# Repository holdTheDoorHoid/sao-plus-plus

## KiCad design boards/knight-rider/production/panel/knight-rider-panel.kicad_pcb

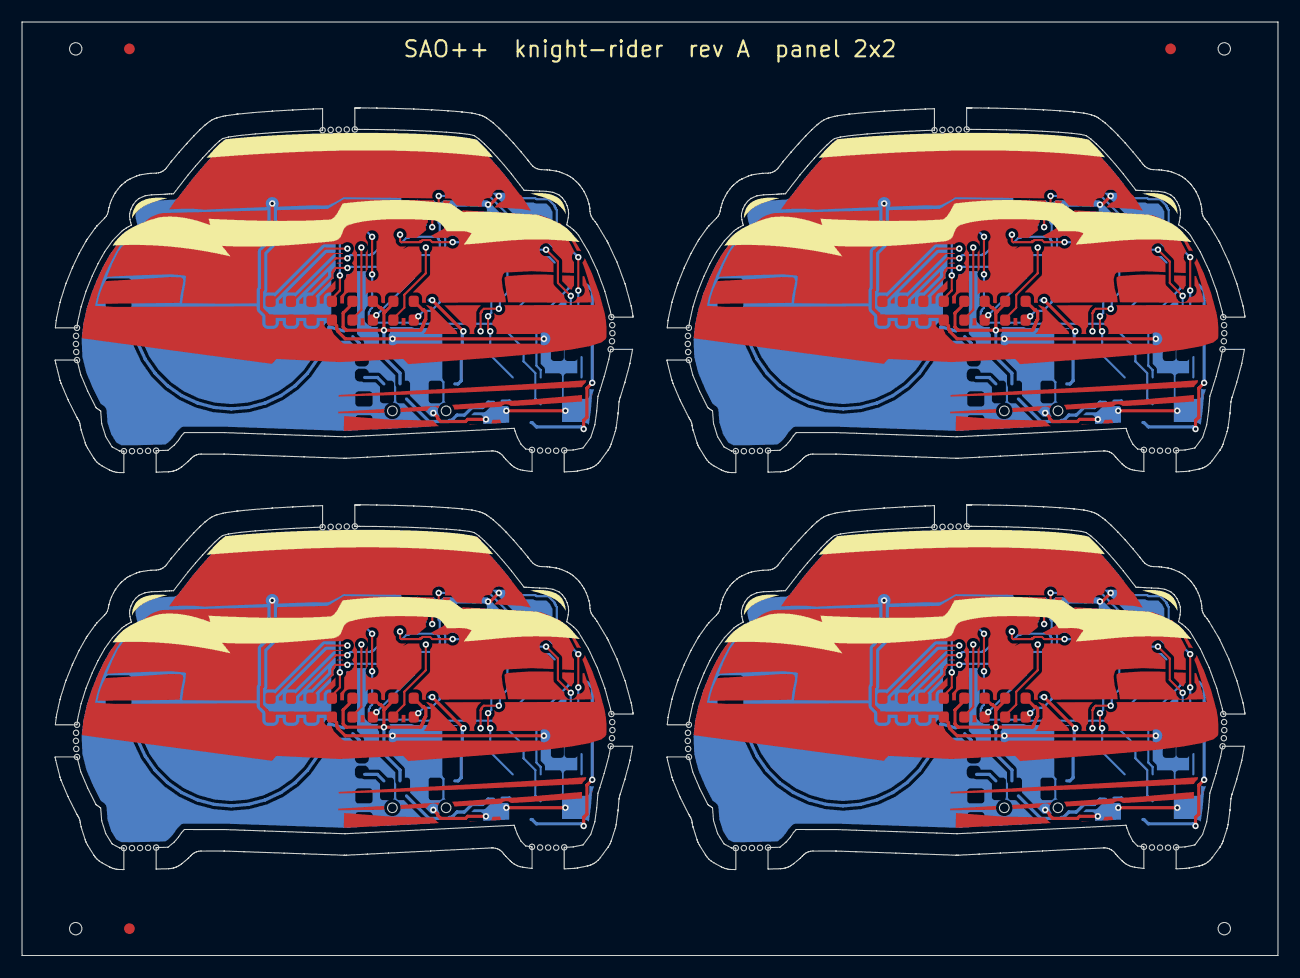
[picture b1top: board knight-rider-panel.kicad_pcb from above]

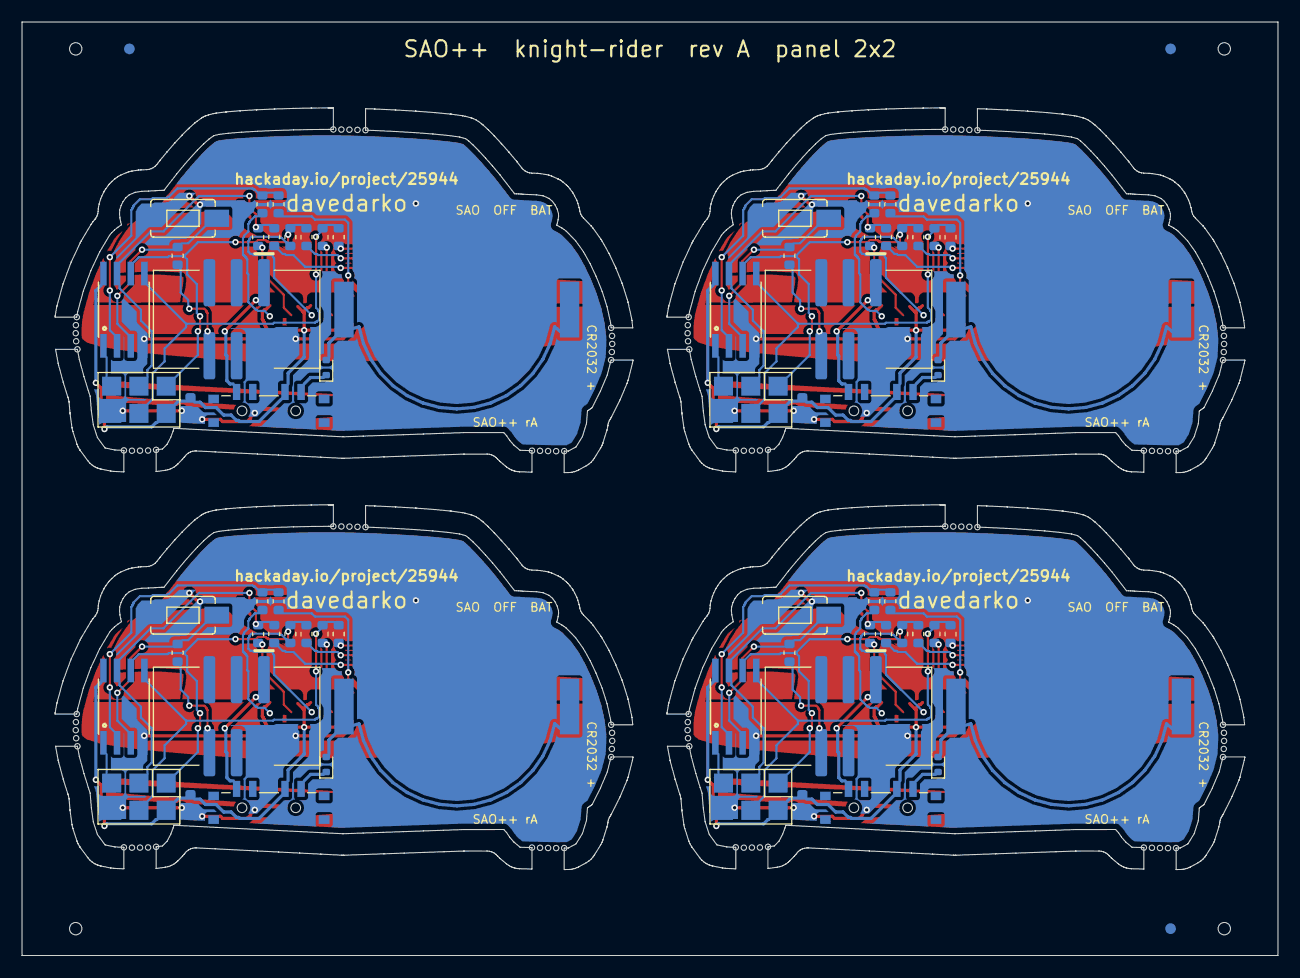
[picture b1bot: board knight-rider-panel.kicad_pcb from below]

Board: 2 copper layers, 117.0 x 86.9 mm, 100 parts (68 on the bottom side), 80 nets.

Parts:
BT101, BT201, BT301, BT401: CR2032; SAOPP_BAT-01_CR2032_SMD_TE_BAT-HLD-001
C101, C201, C301, C401: 100n; SAOPP_C_0603_1608Metric
D101, D102, D103, D104, D105, D106, D107, D108, D201, D202, D203, D204, D205, D206, D207, D208, D301, D302, D303, D304, D305, D306, D307, D308, D401, D402, D403, D404, D405, D406, D407, D408: red; LED_0603_1608Metric_Pad1.05x0.95mm_HandSolder
D109, D209, D309, D409: RB751S40; D_SOD-523
J101, J201, J301, J401: SAO v1.69bis; SAOPP_CONN-01_BoxHeader_2x03_P2.54mm_SMD_XFCN_BH254VS-6P
JP101, JP201, JP301, JP401: ISP pads; 2X3_SMD_PAD
R101, R102, R103, R104, R105, R106, R107, R108, R201, R202, R203, R204, R205, R206, R207, R208, R301, R302, R303, R304, R305, R306, R307, R308, R401, R402, R403, R404, R405, R406, R407, R408: 1.3k; SAOPP_R_0603_1608Metric
R109, R209, R309, R409: 330; SAOPP_R_0603_1608Metric
SW101, SW201, SW301, SW401: SAO / OFF / BAT; SAOPP_SW-01_Slide_SP3T_CK_PCM13SMTR
SW102, SW202, SW302, SW402: button; TACTILE-SWITCH-1101NE
U101, U201, U301, U401: ATtiny85V; SO08-EIAJ

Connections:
B2-GND: BT201.2, C201.2, D201.1, D202.1, D203.1, D204.1, J201.2, JP201.P$6, SW202.P$2, U201.4
B2-LED1_A: D201.2, R205.2
B2-LED2_A: D202.2, R206.2
B2-LED3_A: D203.2, R207.2
B2-LED4_A: D204.2, R208.2
B2-LED5_K: D205.1, R201.2
B2-LED6_K: D206.1, R202.2
B2-LED7_K: D207.1, R203.2
B2-LED8_K: D208.1, R204.2
B2-MISO: JP201.P$1, R202.1, R206.1, U201.6
B2-MOSI: JP201.P$4, R201.1, R205.1, U201.5
B2-PB3: R204.1, R208.1, U201.2
B2-PB4: R209.1, SW202.P$1, U201.3
B2-RST: JP201.P$5, U201.1
B2-SAO_GPIO2: J201.6, R209.2
B2-SCK: JP201.P$3, R203.1, R207.1, U201.7
B2-VBAT: D209.1, SW201.4
B2-VCELL: BT201.1, D209.2
B2-VLOAD: C201.1, D205.2, D206.2, D207.2, D208.2, JP201.P$2, SW201.3, U201.8
B2-VSAO: J201.1, SW201.1
B3-GND: BT301.2, C301.2, D301.1, D302.1, D303.1, D304.1, J301.2, JP301.P$6, SW302.P$2, U301.4
B3-LED1_A: D301.2, R305.2
B3-LED2_A: D302.2, R306.2
B3-LED3_A: D303.2, R307.2
B3-LED4_A: D304.2, R308.2
B3-LED5_K: D305.1, R301.2
B3-LED6_K: D306.1, R302.2
B3-LED7_K: D307.1, R303.2
B3-LED8_K: D308.1, R304.2
B3-MISO: JP301.P$1, R302.1, R306.1, U301.6
B3-MOSI: JP301.P$4, R301.1, R305.1, U301.5
B3-PB3: R304.1, R308.1, U301.2
B3-PB4: R309.1, SW302.P$1, U301.3
B3-RST: JP301.P$5, U301.1
B3-SAO_GPIO2: J301.6, R309.2
B3-SCK: JP301.P$3, R303.1, R307.1, U301.7
B3-VBAT: D309.1, SW301.4
B3-VCELL: BT301.1, D309.2
B3-VLOAD: C301.1, D305.2, D306.2, D307.2, D308.2, JP301.P$2, SW301.3, U301.8
B3-VSAO: J301.1, SW301.1
B4-GND: BT401.2, C401.2, D401.1, D402.1, D403.1, D404.1, J401.2, JP401.P$6, SW402.P$2, U401.4
B4-LED1_A: D401.2, R405.2
B4-LED2_A: D402.2, R406.2
B4-LED3_A: D403.2, R407.2
B4-LED4_A: D404.2, R408.2
B4-LED5_K: D405.1, R401.2
B4-LED6_K: D406.1, R402.2
B4-LED7_K: D407.1, R403.2
B4-LED8_K: D408.1, R404.2
B4-MISO: JP401.P$1, R402.1, R406.1, U401.6
B4-MOSI: JP401.P$4, R401.1, R405.1, U401.5
B4-PB3: R404.1, R408.1, U401.2
B4-PB4: R409.1, SW402.P$1, U401.3
B4-RST: JP401.P$5, U401.1
B4-SAO_GPIO2: J401.6, R409.2
B4-SCK: JP401.P$3, R403.1, R407.1, U401.7
B4-VBAT: D409.1, SW401.4
B4-VCELL: BT401.1, D409.2
B4-VLOAD: C401.1, D405.2, D406.2, D407.2, D408.2, JP401.P$2, SW401.3, U401.8
B4-VSAO: J401.1, SW401.1
GND: BT101.2, C101.2, D101.1, D102.1, D103.1, D104.1, J101.2, JP101.P$6, SW102.P$2, U101.4
LED1_A: D101.2, R105.2
LED2_A: D102.2, R106.2
LED3_A: D103.2, R107.2
LED4_A: D104.2, R108.2
LED5_K: D105.1, R101.2
LED6_K: D106.1, R102.2
LED7_K: D107.1, R103.2
LED8_K: D108.1, R104.2
MISO: JP101.P$1, R102.1, R106.1, U101.6
MOSI: JP101.P$4, R101.1, R105.1, U101.5
PB3: R104.1, R108.1, U101.2
PB4: R109.1, SW102.P$1, U101.3
RST: JP101.P$5, U101.1
SAO_GPIO2: J101.6, R109.2
SCK: JP101.P$3, R103.1, R107.1, U101.7
VBAT: D109.1, SW101.4
VCELL: BT101.1, D109.2
VLOAD: C101.1, D105.2, D106.2, D107.2, D108.2, JP101.P$2, SW101.3, U101.8
VSAO: J101.1, SW101.1

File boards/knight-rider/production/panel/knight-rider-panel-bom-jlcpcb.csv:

Comment,Designator,Footprint,LCSC Part #
CR2032,"BT101,BT201,BT301,BT401",SAOPP_BAT-01_CR2032_SMD_TE_BAT-HLD-001,C7501066
100n,"C101,C201,C301,C401",SAOPP_C_0603_1608Metric,C14663
red,"D101,D102,D103,D104,D105,D106,D107,D108,D201,D202,D203,D204,D205,D206,D207,D208,D301,D302,D303,D304,D305,D306,D307,D308,D401,D402,D403,D404,D405,D406,D407,D408",LED_0603_1608Metric_Pad1.05x0.95mm_HandSolder,C125099
RB751S40,"D109,D209,D309,D409",D_SOD-523,C232576
SAO v1.69bis,"J101,J201,J301,J401",SAOPP_CONN-01_BoxHeader_2x03_P2.54mm_SMD_XFCN_BH254VS-6P,C492445
ISP pads,"JP101,JP201,JP301,JP401",2X3_SMD_PAD,
1.3k,"R101,R102,R103,R104,R105,R106,R107,R108,R201,R202,R203,R204,R205,R206,R207,R208,R301,R302,R303,R304,R305,R306,R307,R308,R401,R402,R403,R404,R405,R406,R407,R408",SAOPP_R_0603_1608Metric,C22767
330,"R109,R209,R309,R409",SAOPP_R_0603_1608Metric,C23138
SAO / OFF / BAT,"SW101,SW201,SW301,SW401",SAOPP_SW-01_Slide_SP3T_CK_PCM13SMTR,C221842
button,"SW102,SW202,SW302,SW402",TACTILE-SWITCH-1101NE,
ATtiny85V,"U101,U201,U301,U401",SO08-EIAJ,C152192

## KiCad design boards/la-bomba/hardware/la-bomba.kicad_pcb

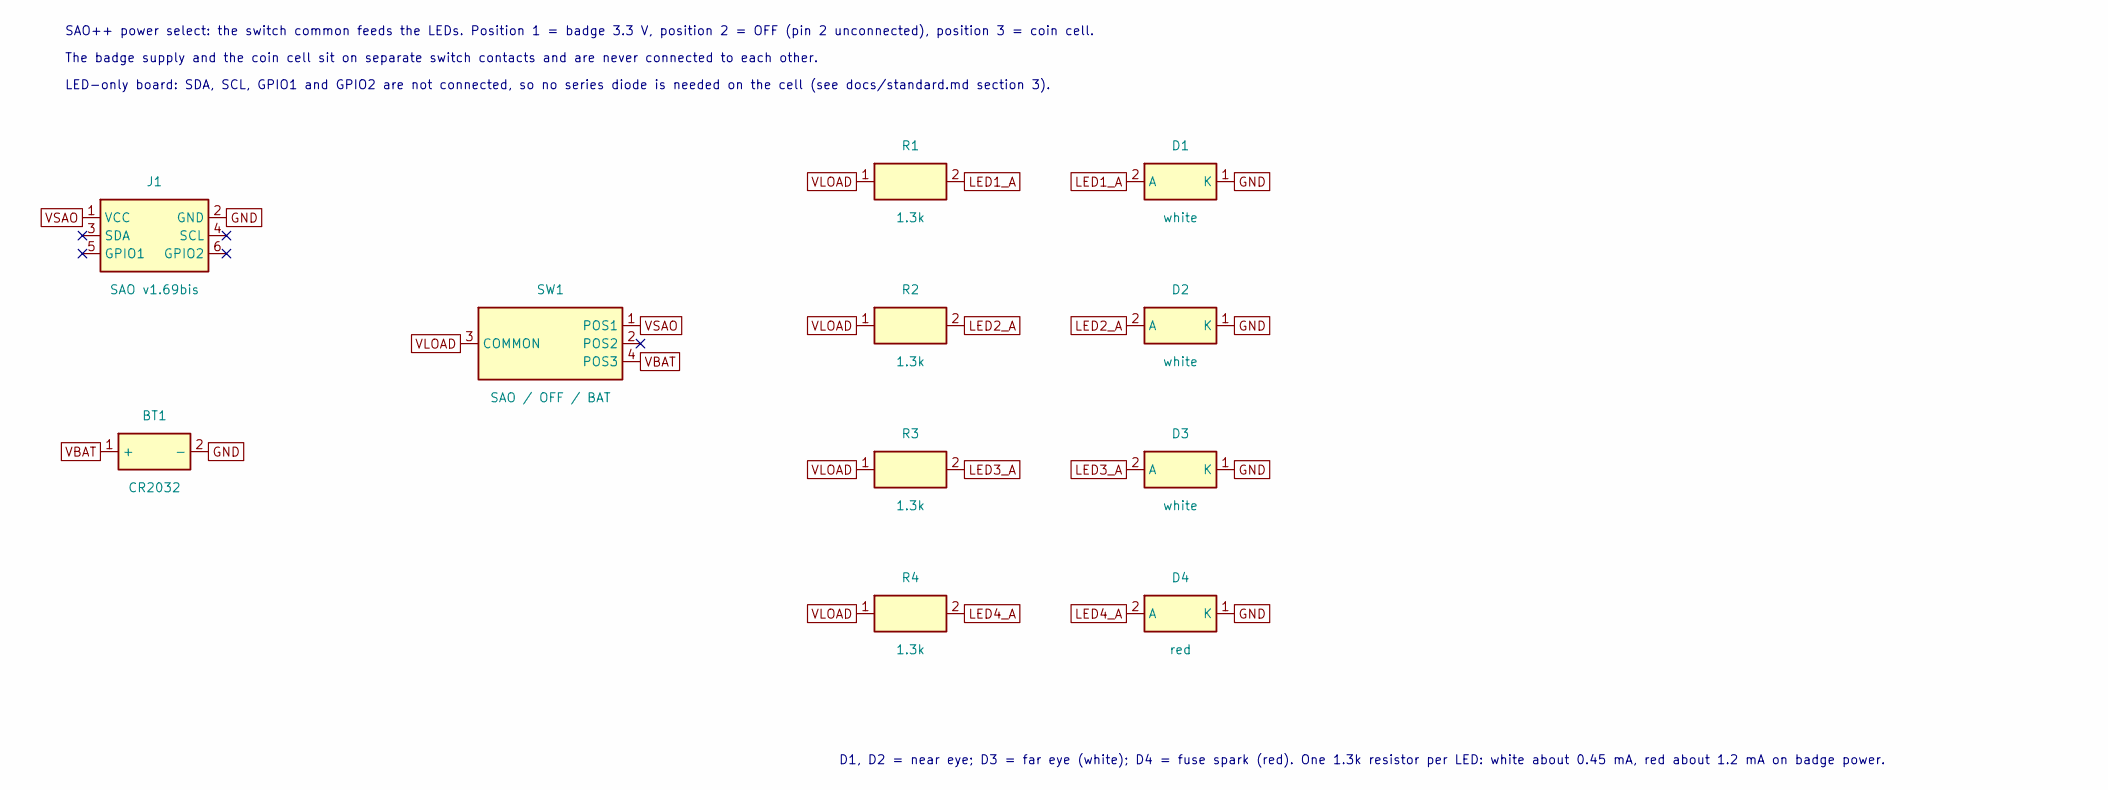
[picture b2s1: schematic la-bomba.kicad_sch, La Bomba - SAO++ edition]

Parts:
BT1: CR2032; SAOPP_BAT-01_CR2032_SMD_TE_BAT-HLD-001; MPN BAT-HLD-001; LCSC C7501066
D1, D2, D3: white; SAOPP_LED-10_1206_ReverseMount_ThroughBoard; MPN LTW-C230DS; LCSC C575513
D4: red; SAOPP_LED-10_1206_ReverseMount_ThroughBoard; MPN LTST-C230KRKT; LCSC C125107
J1: SAO v1.69bis; SAOPP_CONN-01_BoxHeader_2x03_P2.54mm_SMD_XFCN_BH254VS-6P; MPN BH254VS-6P; LCSC C492445
R1, R2, R3, R4: 1.3k; SAOPP_R_0603_1608Metric; MPN 0603WAF1301T5E; LCSC C22767
SW1: SAO / OFF / BAT; SAOPP_SW-01_Slide_SP3T_CK_PCM13SMTR; MPN PCM13SMTR; LCSC C221842

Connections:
GND: BT1.2 (-), D1.1 (K), D2.1 (K), D3.1 (K), D4.1 (K), J1.2 (GND)
LED1_A: D1.2 (A), R1.2
LED2_A: D2.2 (A), R2.2
LED3_A: D3.2 (A), R3.2
LED4_A: D4.2 (A), R4.2
VBAT: BT1.1 (+), SW1.4 (POS3)
VLOAD: R1.1, R2.1, R3.1, R4.1, SW1.3 (COMMON)
VSAO: J1.1 (VCC), SW1.1 (POS1)

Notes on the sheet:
SAO++ power select: the switch common feeds the LEDs. Position 1 = badge 3.3 V, position 2 = OFF (pin 2 unconnected), position 3 = coin cell.
The badge supply and the coin cell sit on separate switch contacts and are never connected to each other.
LED-only board: SDA, SCL, GPIO1 and GPIO2 are not connected, so no series diode is needed on the cell (see docs/standard.md section 3).
D1, D2 = near eye; D3 = far eye (white); D4 = fuse spark (red). One 1.3k resistor per LED: white about 0.45 mA, red about 1.2 mA on badge power.

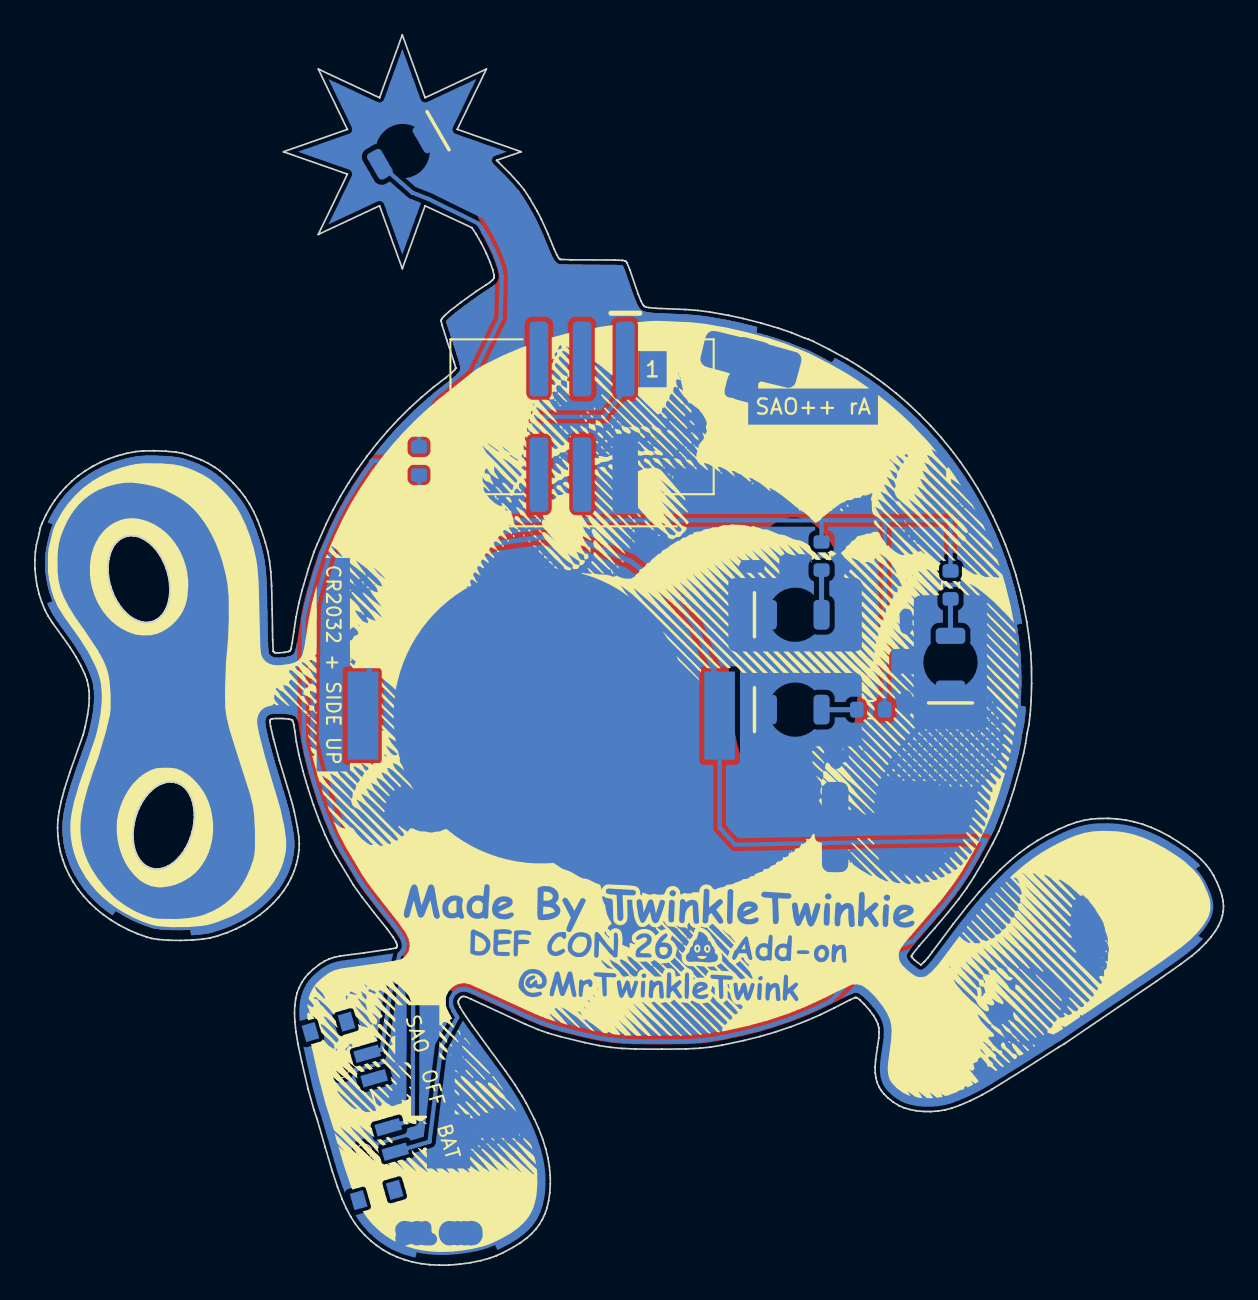
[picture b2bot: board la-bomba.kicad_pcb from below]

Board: 2 copper layers, 70.0 x 72.5 mm, 15 parts (11 on the bottom side), 8 nets.

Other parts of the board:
B.Silk: LOGO; B.Silk_g1544
F.Cu, F.Silk: LOGO
F.Mask: LOGO; F.Mask_g1548

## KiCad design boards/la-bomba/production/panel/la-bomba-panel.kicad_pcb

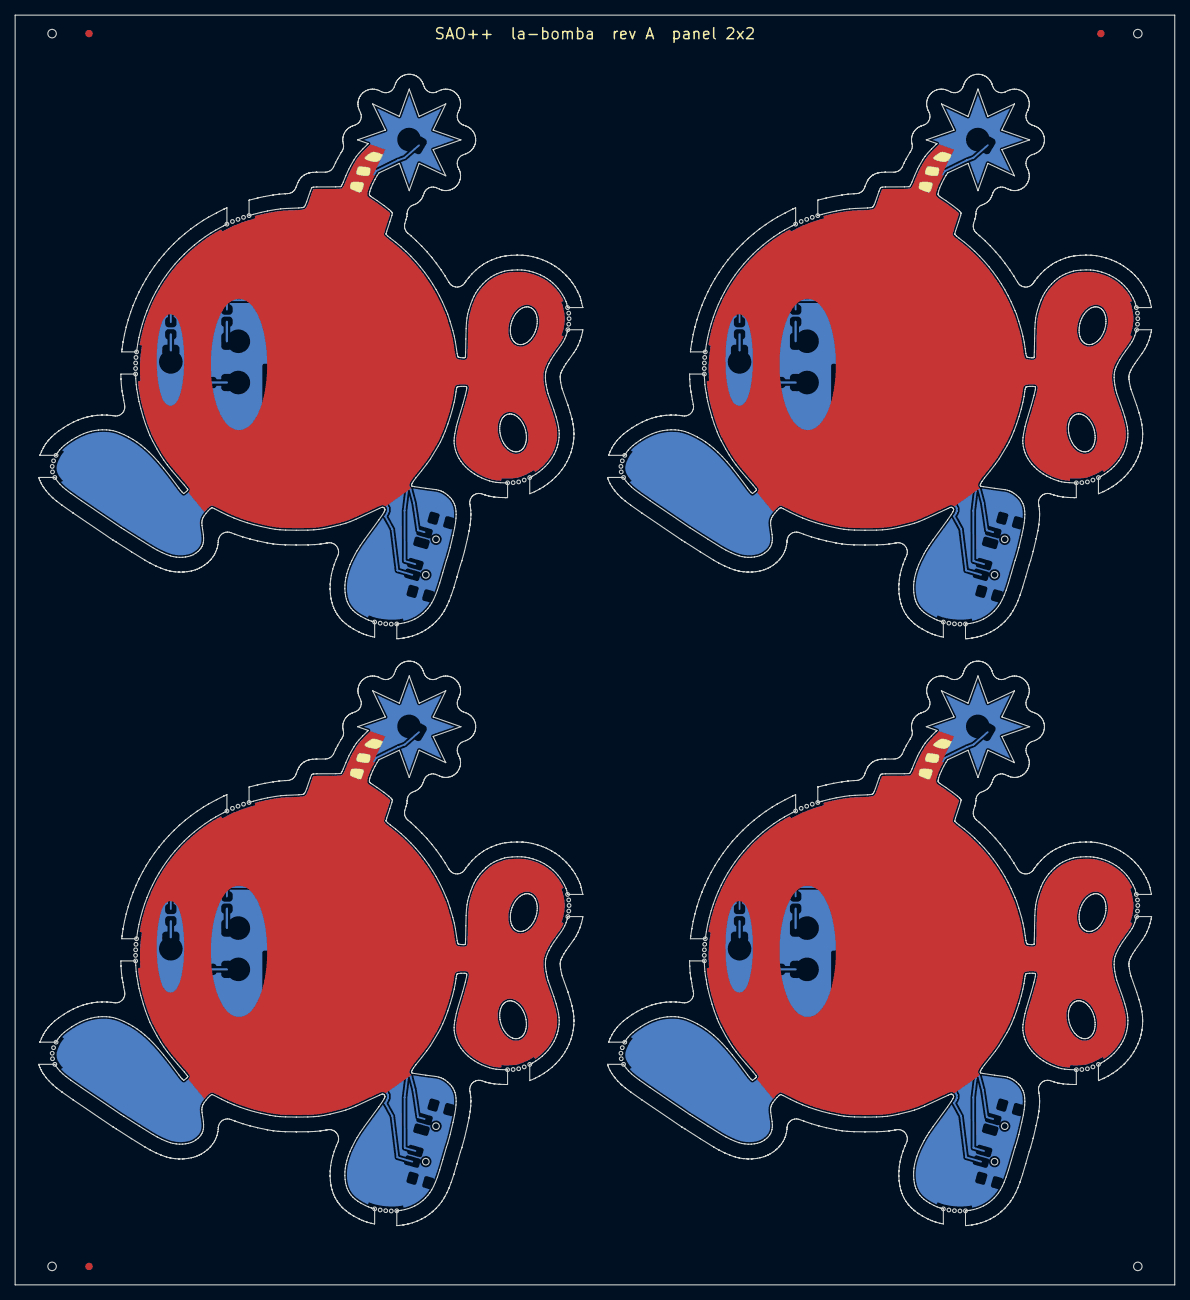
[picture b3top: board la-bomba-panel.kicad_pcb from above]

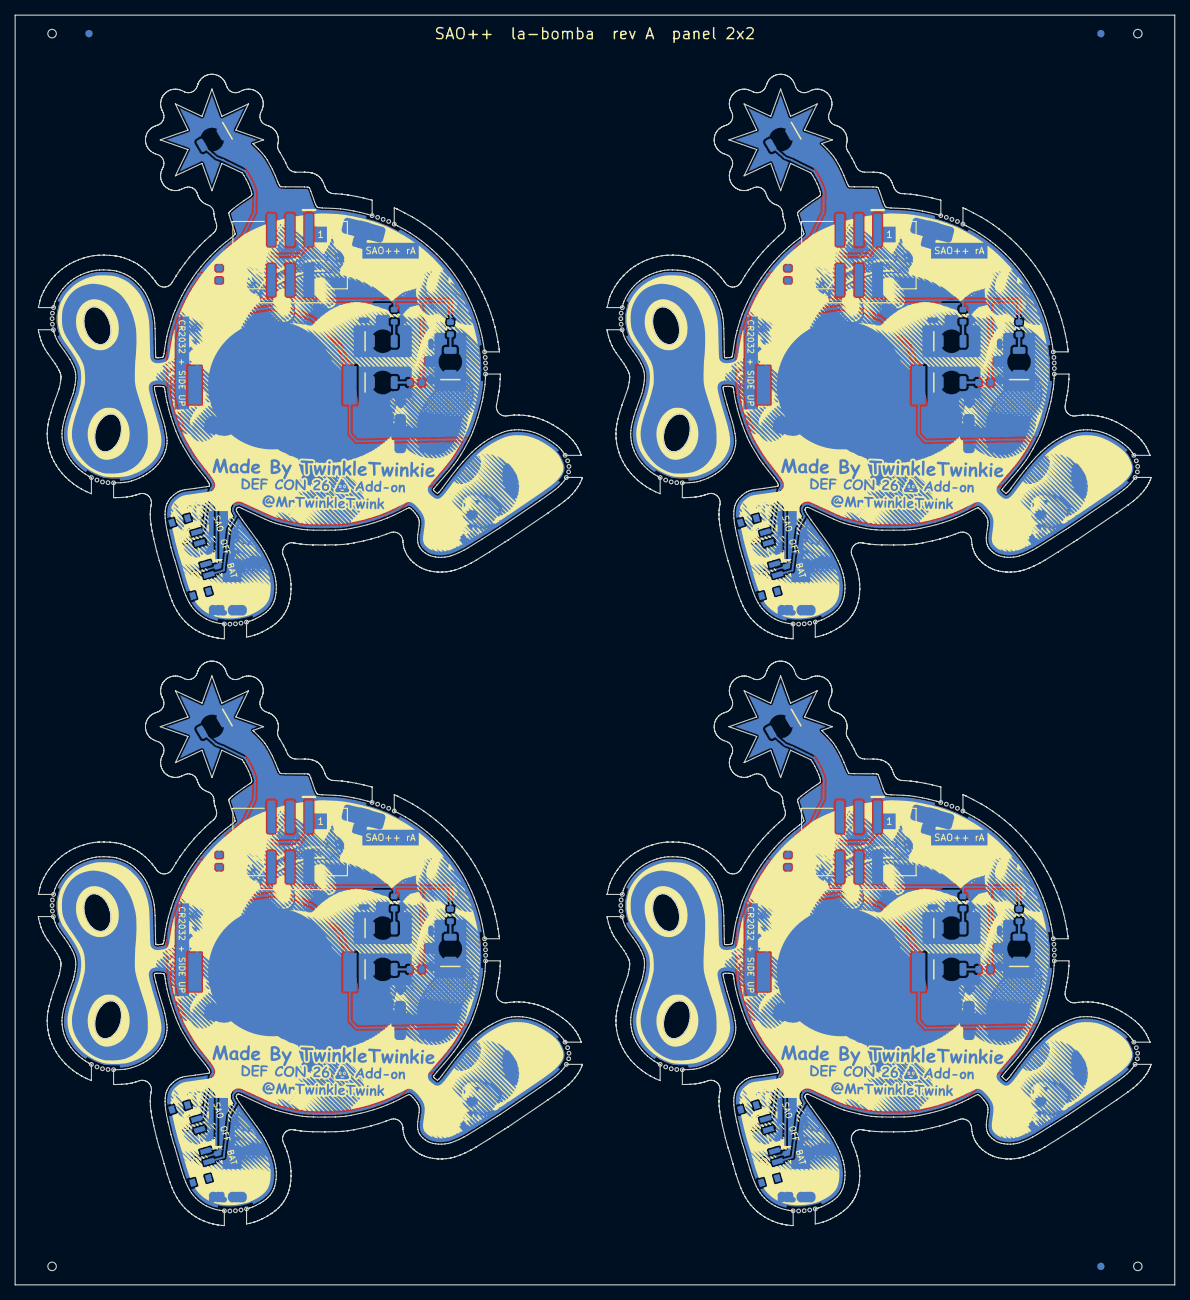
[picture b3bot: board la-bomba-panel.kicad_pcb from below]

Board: 2 copper layers, 157.0 x 171.9 mm, 60 parts (44 on the bottom side), 32 nets.

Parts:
B.Silk, B.Silk#2, B.Silk#3, B.Silk#4: LOGO; B.Silk_g1544
BT101, BT201, BT301, BT401: CR2032; SAOPP_BAT-01_CR2032_SMD_TE_BAT-HLD-001
D101, D102, D103, D201, D202, D203, D301, D302, D303, D401, D402, D403: white; SAOPP_LED-10_1206_ReverseMount_ThroughBoard
D104, D204, D304, D404: red; SAOPP_LED-10_1206_ReverseMount_ThroughBoard
F.Cu, F.Cu#2, F.Cu#3, F.Cu#4, F.Silk, F.Silk#2, F.Silk#3, F.Silk#4: LOGO
F.Mask, F.Mask#2, F.Mask#3, F.Mask#4: LOGO; F.Mask_g1548
J101, J201, J301, J401: SAO v1.69bis; SAOPP_CONN-01_BoxHeader_2x03_P2.54mm_SMD_XFCN_BH254VS-6P
R101, R102, R103, R104, R201, R202, R203, R204, R301, R302, R303, R304, R401, R402, R403, R404: 1.3k; SAOPP_R_0603_1608Metric
SW101, SW201, SW301, SW401: SAO / OFF / BAT; SAOPP_SW-01_Slide_SP3T_CK_PCM13SMTR

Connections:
B2-GND: BT201.2, D201.1, D202.1, D203.1, D204.1, J201.2
B2-LED1_A: D201.2, R201.2
B2-LED2_A: D202.2, R202.2
B2-LED3_A: D203.2, R203.2
B2-LED4_A: D204.2, R204.2
B2-VBAT: BT201.1, SW201.4
B2-VLOAD: R201.1, R202.1, R203.1, R204.1, SW201.3
B2-VSAO: J201.1, SW201.1
B3-GND: BT301.2, D301.1, D302.1, D303.1, D304.1, J301.2
B3-LED1_A: D301.2, R301.2
B3-LED2_A: D302.2, R302.2
B3-LED3_A: D303.2, R303.2
B3-LED4_A: D304.2, R304.2
B3-VBAT: BT301.1, SW301.4
B3-VLOAD: R301.1, R302.1, R303.1, R304.1, SW301.3
B3-VSAO: J301.1, SW301.1
B4-GND: BT401.2, D401.1, D402.1, D403.1, D404.1, J401.2
B4-LED1_A: D401.2, R401.2
B4-LED2_A: D402.2, R402.2
B4-LED3_A: D403.2, R403.2
B4-LED4_A: D404.2, R404.2
B4-VBAT: BT401.1, SW401.4
B4-VLOAD: R401.1, R402.1, R403.1, R404.1, SW401.3
B4-VSAO: J401.1, SW401.1
GND: BT101.2, D101.1, D102.1, D103.1, D104.1, J101.2
LED1_A: D101.2, R101.2
LED2_A: D102.2, R102.2
LED3_A: D103.2, R103.2
LED4_A: D104.2, R104.2
VBAT: BT101.1, SW101.4
VLOAD: R101.1, R102.1, R103.1, R104.1, SW101.3
VSAO: J101.1, SW101.1

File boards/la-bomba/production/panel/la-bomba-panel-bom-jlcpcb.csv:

Comment,Designator,Footprint,LCSC Part #
CR2032,"BT101,BT201,BT301,BT401",SAOPP_BAT-01_CR2032_SMD_TE_BAT-HLD-001,C7501066
white,"D101,D102,D103,D201,D202,D203,D301,D302,D303,D401,D402,D403",SAOPP_LED-10_1206_ReverseMount_ThroughBoard,C575513
red,"D104,D204,D304,D404",SAOPP_LED-10_1206_ReverseMount_ThroughBoard,C125107
SAO v1.69bis,"J101,J201,J301,J401",SAOPP_CONN-01_BoxHeader_2x03_P2.54mm_SMD_XFCN_BH254VS-6P,C492445
1.3k,"R101,R102,R103,R104,R201,R202,R203,R204,R301,R302,R303,R304,R401,R402,R403,R404",SAOPP_R_0603_1608Metric,C22767
SAO / OFF / BAT,"SW101,SW201,SW301,SW401",SAOPP_SW-01_Slide_SP3T_CK_PCM13SMTR,C221842

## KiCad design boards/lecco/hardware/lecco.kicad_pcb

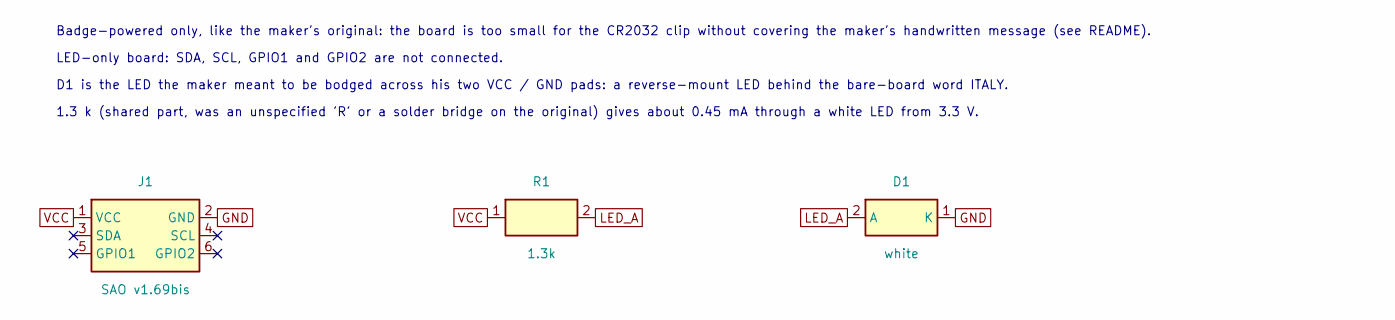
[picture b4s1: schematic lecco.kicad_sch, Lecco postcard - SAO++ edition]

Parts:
D1: white; SAOPP_LED-10_1206_ReverseMount_ThroughBoard; MPN LTW-C230DS; LCSC C575513
J1: SAO v1.69bis; SAOPP_CONN-01_BoxHeader_2x03_P2.54mm_SMD_XFCN_BH254VS-6P; MPN BH254VS-6P; LCSC C492445
R1: 1.3k; SAOPP_R_0603_1608Metric; MPN 0603WAF1301T5E; LCSC C22767

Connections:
GND: D1.1 (K), J1.2 (GND)
LED_A: D1.2 (A), R1.2
VCC: J1.1 (VCC), R1.1

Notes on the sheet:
Badge-powered only, like the maker's original: the board is too small for the CR2032 clip without covering the maker's handwritten message (see README).
LED-only board: SDA, SCL, GPIO1 and GPIO2 are not connected.
D1 is the LED the maker meant to be bodged across his two VCC / GND pads: a reverse-mount LED behind the bare-board word ITALY.
1.3 k (shared part, was an unspecified 'R' or a solder bridge on the original) gives about 0.45 mA through a white LED from 3.3 V.

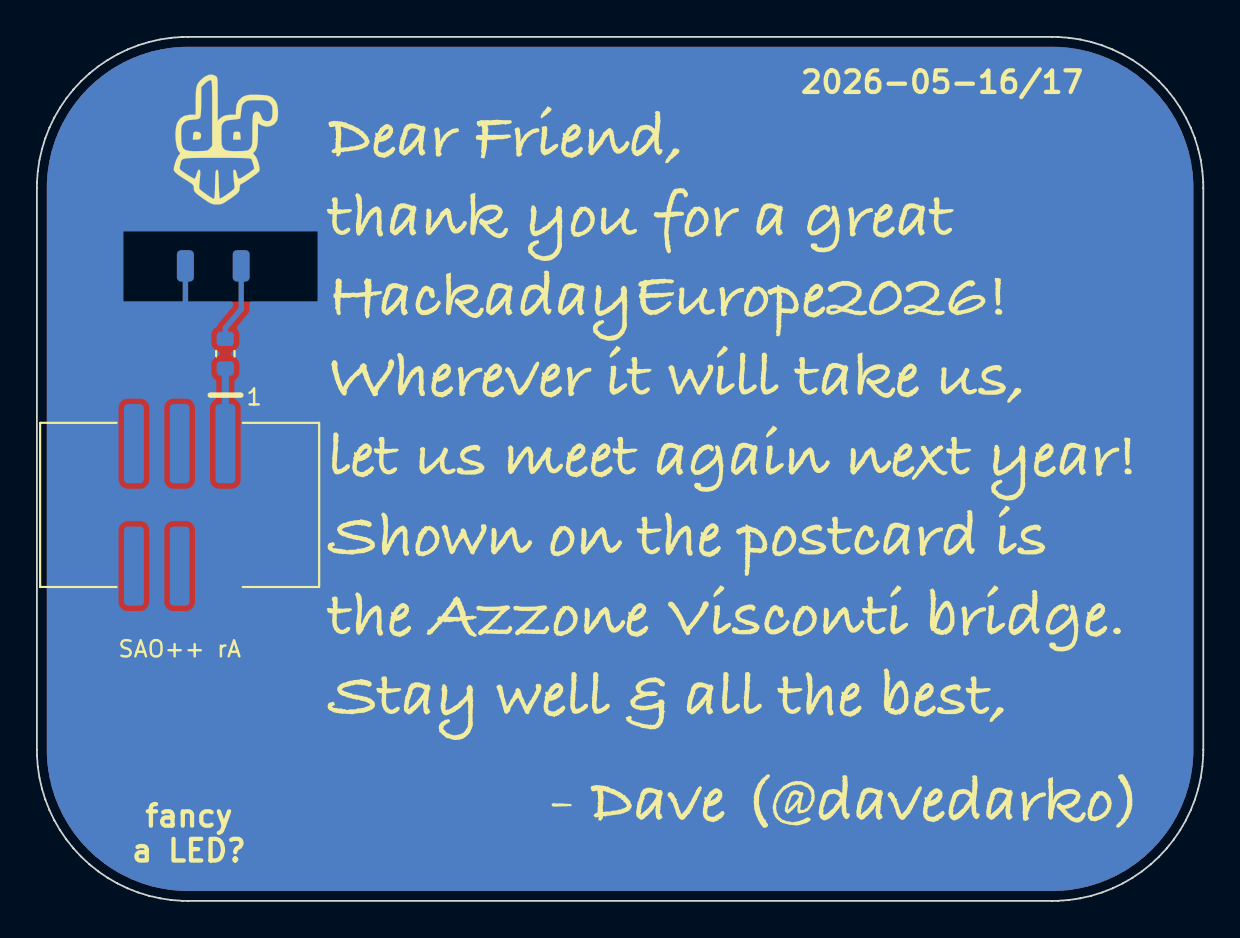
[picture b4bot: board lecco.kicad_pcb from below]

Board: 2 copper layers, 64.8 x 48.0 mm, 4 parts (4 on the bottom side), 3 nets.

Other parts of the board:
Ref**: Val**; davedarko_logo_silk_outline

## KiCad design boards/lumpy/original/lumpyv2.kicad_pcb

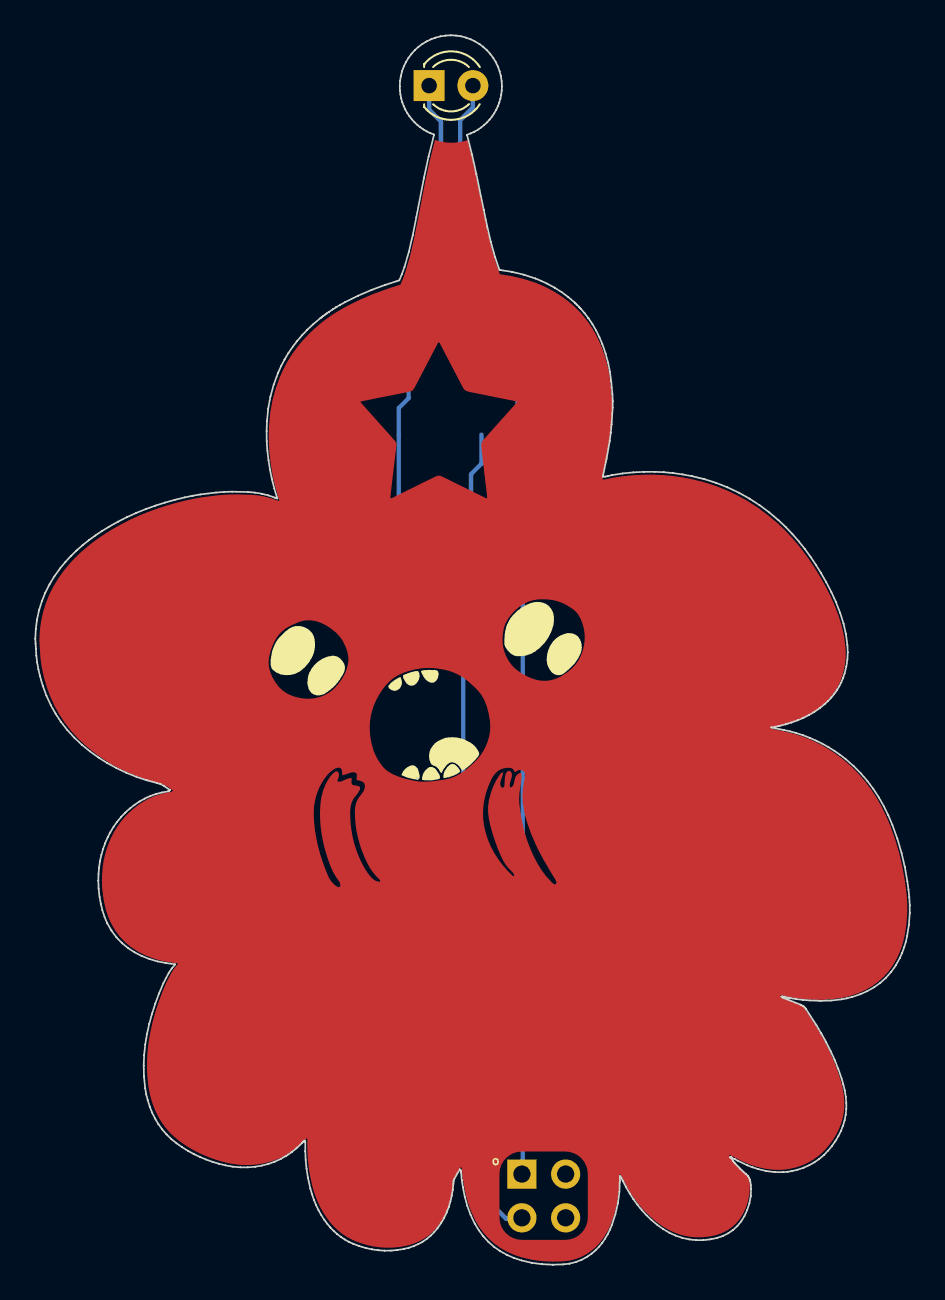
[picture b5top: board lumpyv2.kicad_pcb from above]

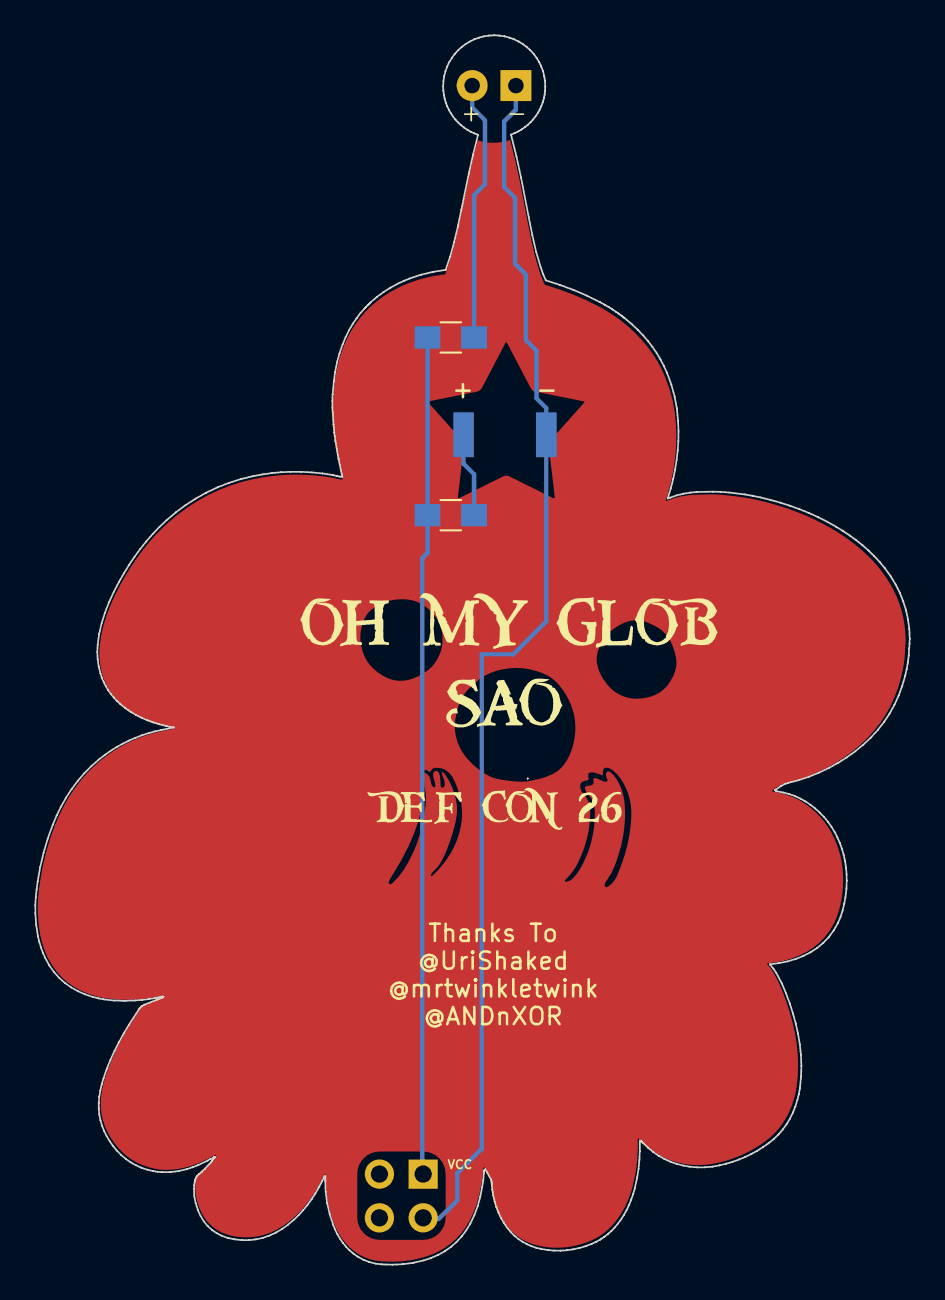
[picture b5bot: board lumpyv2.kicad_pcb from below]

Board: 2 copper layers, 50.8 x 71.4 mm, 8 parts (5 on the bottom side), 4 nets.

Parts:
D1: LED; LED_D3.0mm
D2: LED; LED_OSRAM_TOPLED_LxT776
J1: Conn_02x02_Odd_Even; PinHeader_2x02_P2.54mm_Vertical_edit
R1, R2: R; R_0805_HandSoldering
svg2mod: G***; lumpyTop
svg2mod#2: G***; lumpyBottom
svg2mod#3: G***; lumpyback

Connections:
unnamed: D1.1, D2.1, J1.3
unnamed: D1.2, R1.1
unnamed: D2.2, R2.1
unnamed: J1.1, R1.2, R2.2
